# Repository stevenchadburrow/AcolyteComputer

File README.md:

# AcolyteComputer
Acolyte 6502 "Homebrew" Computer

Runs a W65C02 Microprocessor at 3.14 MHz.
Has 64K SRAM and 32K FlashROM.

VGA resolution of 320x240 4-Colors.
PS/2 Keyboard support built in.
One-voice square wave audio.
SPI EEPROM is built into the board.
Socket for a MicroSD Card Adapter.
Optional VIA Expansion.
It is powered with 5V USB.

The goal is that this board would cost less than $100 to assemble.
There are also no CPLD or FPGA chips used, everything besides the 6502/RAM/ROM are 74HC' logic chips.

All files included here are hereby released into the Public Domain.  Anyone is free to copy, modify, publish, use, compile, sell, or distribute these files for any purpose, commercial or non-commercial, and by any means.  These files are provided "as is", without warranty of any kind.  In no event shall the author be liable for any claim, damages, or other liability.

<br>
<br>
<br>
<br>

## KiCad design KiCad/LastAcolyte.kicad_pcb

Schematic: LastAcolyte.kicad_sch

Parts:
C1: C_Polarized_US; Dual Capacitor (Medium)
C2: C-Polarized-US; Dual Electrolytic Capacitor
C3, C4, C5, C6, C7, C8, C9, C10, C11, C12, C13, C14, C15, C16, C17, C18, C19, C20, C21, C22: C; C_Disc_D5.0mm_W2.5mm_P5.00mm
D1: LED; CustomLED
D2, D3: D; WideDiode
J1: USB_B; DualPowerSupply
J2: Mini-DIN-6; PS2_Din6
J3: AudioJack3; BIGJack_3.5mm_Ledino_KB3SPRS_Horizontal
J4: DB15_Female_HighDensity; DSUB-15-HD_Female_Horizontal_P2.29x2.54mm_VGA
J5: Conn-01x06; SDcardPinSocket-Wide
J6: Conn_01x02; PinHeader_1x02_P2.54mm_Vertical
J7: Conn_02x20_Odd_Even; PinSocket_2x20_P2.54mm_Vertical
JP1, JP2: SolderJumper_2_Open; SolderJumper_Testing-2_P1.3mm_Open_Pad1.0x1.5mm
Q1, Q2, Q3: PN2222A; TO-92_HandSolder
R1, R4, R5, R6, R7, R8, R9, R10, R11, R12, R13, R14, R16, R17, R18, R19, R20: R_US; R_Axial_DIN0207_L6.3mm_D2.5mm_P7.62mm_Horizontal
R2, R3: R-US; R_Axial_DIN0207_L6.3mm_D2.5mm_P7.62mm_Horizontal
SW1: SW_SPDT; SPDT-1MS1T1B4M7QES
SW2: SW_Push; SW_Tactile_SPST_Angled_PTS645Vx83-2LFS
TP1, TP2, TP3, TP4, TP5: TestPoint; ScrewHole-4-40
TP6, TP7: TestPoint; CustomTestPoint
U1: W65C02SxP; DIP-40_W15.24mm_Socket
U2: AS6C4008-55PCN; DIP-32_W15.24mm_Socket
U3: SST39SF040; DIP-32_W15.24mm_Socket
U4: 74HC161; DIP-16_W7.62mm_Socket
U5, U6, U7: 74HC590; DIP-16_W7.62mm_Socket
U8: 74HC245; DIP-20_W7.62mm_Socket
U9: 74HC273; DIP-20_W7.62mm_Socket
U10: 74HC377; DIP-20_W7.62mm_Socket
U11, U12: 74HC166; DIP-16_W7.62mm_Socket
U13: 74HC10; DIP-14_W7.62mm_Socket
U14: 74HC08; DIP-14_W7.62mm_Socket
U15: 74HC00; DIP-14_W7.62mm_Socket
U16: 74HC02; DIP-14_W7.62mm_Socket
U17: MCP130-xxxDxTO; TO-92_HandSolder
U18: 25LCxxx; DIP-8_W7.62mm_Socket
X1: CXO_DIP8/14; DualOscillator

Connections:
+5V: C1.1, C3.1, C4.1, C5.1, C6.1, C7.1, C8.1, C9.1, C10.1, C11.1, C12.1, C13.1, C14.1, C15.1, C16.1, C17.1, C18.1, C19.1, C20.1, C21.1, C22.1, J2.4, J5.2, J6.1, J7.1, J7.40, JP1.1 (A), JP2.2 (B), R1.2, R4.1, R5.1, R6.1, R7.2, R8.2, R16.2, R17.1, R18.1, R19.1, R20.2, SW1.2 (B), U1.8 (VDD), U2.1 (A18), U2.30 (A17), U2.32 (VCC), U3.1 (A18), U3.30 (A17), U3.31 (PGM), U3.32 (VCC), U4.1 (~MR), U4.3 (D0), U4.4 (D1), U4.5 (D2), U4.6 (D3), U4.7 (CEP), U4.9 (~PE), U4.10 (CET), U4.16 (VCC), U5.16 (VCC), U6.16 (VCC), U7.16 (VCC), U8.20 (VCC), U9.20 (VCC), U10.20 (VCC), U11.16 (VCC), U12.16 (VCC), U13.14 (VCC), U14.14 (VCC), U15.14 (VCC), U16.14 (VCC), U17.2 (VDD), U18.3 (~WP), U18.7 (~HOLD), U18.8 (VCC), X1.11 (Vcc), X1.14 (Vcc)
/D0: U1.33 (D0), U3.13 (D0), U8.18 (B0), U9.3 (D0), U10.3 (D0)
/D1: U1.32 (D1), U3.14 (D1), U8.17 (B1), U9.4 (D1), U10.4 (D1)
/D2: U1.31 (D2), U3.15 (D2), U8.16 (B2), U9.7 (D2), U10.7 (D2)
/D3: U1.30 (D3), U3.17 (D3), U8.15 (B3), U9.8 (D3), U10.8 (D3)
/D4: U1.29 (D4), U3.18 (D4), U8.14 (B4), U9.13 (D4), U10.13 (D4)
/D5: U1.28 (D5), U3.19 (D5), U8.13 (B5), U9.14 (D5), U10.14 (D5)
/D6: U1.27 (D6), U3.20 (D6), U8.12 (B6), U9.17 (D6), U10.17 (D6)
/D7: U1.26 (D7), U3.21 (D7), U8.11 (B7), U9.18 (D7), U10.18 (D7)
A0: J7.38, U1.9 (A0), U2.12 (A0), U3.12 (A0), U5.15 (Q0)
A1: J7.36, U1.10 (A1), U2.11 (A1), U3.11 (A1), U5.1 (Q1)
A2: J7.34, U1.11 (A2), U2.10 (A2), U3.10 (A2), U5.2 (Q2)
A3: J7.32, U1.12 (A3), U2.9 (A3), U3.9 (A3), U5.3 (Q3)
A4: J7.30, U1.13 (A4), U2.8 (A4), U3.8 (A4), U5.4 (Q4)
A5: J7.28, U1.14 (A5), U2.7 (A5), U3.7 (A5), U5.5 (Q5)
A6: J7.26, U1.15 (A6), U2.6 (A6), U3.6 (A6), U5.6 (Q6)
A7: J7.24, U1.16 (A7), U2.5 (A7), U3.5 (A7), U6.1 (Q1)
A8: J7.18, U1.17 (A8), U2.27 (A8), U3.27 (A8), U6.2 (Q2)
A9: J7.16, U1.18 (A9), U2.26 (A9), U3.26 (A9), U6.3 (Q3)
A10: J7.14, U1.19 (A10), U2.23 (A10), U3.23 (A10), U6.4 (Q4)
A11: J7.12, U1.20 (A11), U2.25 (A11), U3.25 (A11), U6.5 (Q5)
A12: U1.22 (A12), U2.4 (A12), U3.4 (A12), U6.6 (Q6), U14.2
A13: U1.23 (A13), U2.28 (A13), U3.28 (A13), U6.7 (Q7), U14.1
A14: U1.24 (A14), U2.3 (A14), U3.29 (A14), U7.15 (Q0), U14.13, U16.2
A15: U1.25 (A15), U2.31 (A15), U3.3 (A15), U7.1 (Q1), U13.10, U14.12, U15.1
AUDIO-NEG: C2.2, R2.2
AUDIO-OUT: C2.1, J7.21, U9.19 (Q7)
AUDIO-TIP: J3.T, R2.1, R3.1
BE: U1.36 (BE), U1.39 (ϕ2)
BLUE: J4.3, R11.2, R14.2
C0: J7.3, U2.13 (DQ0), U8.2 (A0), U12.2 (A), U12.3 (B)
C1: J7.5, U2.14 (DQ1), U8.3 (A1), U11.2 (A), U11.3 (B)
C2: J7.7, U2.15 (DQ2), U8.4 (A2), U12.4 (C), U12.5 (D)
C3: J7.9, U2.17 (DQ3), U8.5 (A3), U11.4 (C), U11.5 (D)
C4: J7.11, U2.18 (DQ4), U8.6 (A4), U12.10 (E), U12.11 (F)
C5: J7.13, U2.19 (DQ5), U8.7 (A5), U11.10 (E), U11.11 (F)
C6: J7.15, U2.20 (DQ6), U8.8 (A6), U12.12 (G), U12.14 (H)
C7: J7.17, U2.21 (DQ7), U8.9 (A7), U11.12 (G), U11.14 (H)
CLK: J7.29, U4.2 (CP), U5.13 (CPR), U6.13 (CPR), U7.13 (CPR), U10.11 (CP), U11.7 (Clk), U12.7 (Clk), X1.8 (OUT)
ENABLE: JP1.2 (B), X1.1 (EN), X1.4 (EN)
GND: C1.2, C3.2, C4.2, C5.2, C6.2, C7.2, C8.2, C9.2, C10.2, C11.2, C12.2, C13.2, C14.2, C15.2, C16.2, C17.2, C18.2, C19.2, C20.2, C21.2, C22.2, D1.1 (K), J1.4 (GND), J1.5 (Shield), J1.7 (Barrel_GND), J2.3, J3.S, J4.5, J4.6, J4.7, J4.8, J4.10, J5.1, J6.2, J7.2, J7.19, J7.22, J7.39, Q1.1 (E), Q2.1 (E), R3.2, SW1.4 (Shield), SW2.2, TP1.1, TP2.1, TP3.1, TP4.1, TP5.1, TP6.1, TP7.1, U1.21 (VSS), U2.16 (VSS), U3.16 (GND), U4.8 (GND), U5.8 (GND), U5.12 (~CE), U6.8 (GND), U6.12 (~CE), U7.8 (GND), U8.10 (GND), U9.10 (GND), U10.10 (GND), U11.1 (Ds), U11.6 (CE), U11.8 (GND), U12.1 (Ds), U12.6 (CE), U12.8 (GND), U13.7 (GND), U14.7 (GND), U15.7 (GND), U16.7 (GND), U17.3 (VSS), U18.4 (GND), X1.7 (GND)
GREEN: J4.2, R10.2, R13.2
H-RESET: U5.10 (~MRC), U10.2 (Q0)
H-SYNC: J4.13, U10.12 (Q4)
HALF: J7.27, U4.14 (Q0), U13.1
HIGH: U14.11, U15.4, U16.9
IO-ENABLE: U9.15 (Q5), U16.3
IO-INT: D3.1 (K), J7.8, R20.1
KEY-CLK: J2.5, R4.2, U14.4
KEY-DATA: D2.1 (K), J2.1, R5.2
LED: D1.2 (A), R1.1
MEM-BANK: U3.2 (A16), U9.12 (Q4), U15.2
MID: U13.11, U14.3
NMI-ENABLE: U9.16 (Q6), U14.5
PHI2: J7.23, U1.37 (ϕ0), U4.12 (Q2), U5.11 (CPC), U5.14 (~OE), U6.14 (~OE), U7.14 (~OE), U15.9
PIXA: R9.1, R10.1, R11.1, U11.13 (Qh)
PIXB: R12.1, R13.1, R14.1, U12.13 (Qh)
POWER-IN: J1.1 (VBUS), J1.6 (Barrel_VCC), JP2.1 (A), SW1.1 (A)
QUARTER: J7.25, U4.13 (Q1), U13.2, U13.3
RAMADDR: U13.5, U14.8, U16.11
RAMEXP: U2.2 (A16), U15.3
RDY: J7.31, R7.1, U1.2 (RDY)
RED: J4.1, R9.2, R12.2
SIXTEENTH: U4.11 (Q3), U15.13
SPI-CLK: J5.5, U9.2 (Q0), U18.6 (SCK)
SPI-EEPROM: U9.6 (Q2), U18.1 (~CS)
SPI-MISO: J7.4, Q1.2 (B), Q3.1 (E), R8.1, U18.2 (MISO)
SPI-MOSI: J5.4, U9.5 (Q1), U18.5 (MOSI)
SPI-SDCARD: J5.6, Q2.2 (B), U9.9 (Q3)
SPI-SDCARD-MISO: J5.3, Q3.3 (C)
SYNC: J7.37, U1.7 (SYNC)
V-BLANK: U10.19 (Q7)
V-RESET: U6.10 (~MRC), U7.10 (~MRC), U10.6 (Q2)
V-SYNC: J4.14, U10.15 (Q5)
VISIBLE: U10.16 (Q6), U11.9 (Clr), U12.9 (Clr)
~A14: U13.9, U16.1
~CE: U8.19 (CE), U15.8
~H-RESET: U6.11 (CPC), U7.11 (CPC), U10.5 (Q1)
~IO: J7.10, U13.8, U14.9
~IRQ: D2.2 (A), D3.2 (A), R16.1, U1.4 (~IRQ)
~LATCH: U10.1 (~E), U11.15 (PE), U12.15 (PE), U13.12
~NMI: U1.6 (~NMI), U14.6
~OE: J7.33, U2.24 (OE#), U3.24 (OE), U13.4, U15.5, U16.4
~OUTPUT: U9.11 (Cp), U15.6
~PHI2: U1.3 (ϕ1), U13.13, U16.5, U16.8, U16.12
~RAM: U2.22 (CE#), U16.13
~RCO: U6.9 (~RCO), U7.12 (~CE)
~RES: J7.6, R18.2, SW2.1, U1.40 (~RES), U9.1 (~Mr), U17.1 (~RST)
~ROM: U3.22 (CE), U14.10, U15.10, U16.10
~RW: J7.35, R6.2, U1.34 (R/~W), U8.1 (A->B), U16.6
~SO: U1.38 (~SO), U15.11
~SPI-MISO: Q1.3 (C), R17.2, U15.12
~SPI-SDCARD: Q2.3 (C), Q3.2 (B), R19.2
~V-RESET: U10.9 (Q3)
~WE: U2.29 (WE#), U13.6

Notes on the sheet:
W65C02 running at 3.14 MHz 2KB System RAM 30KB Video RAM 12KB Banked RAM 4KB I/O (or RAM) 16KB Banked ROM
Video signals from ROM.
0.1uF Bypass Capacitors near VCC of each IC
Acolyte Computer Steven Chad Burrow 2023, Public Domain
~{CS2}
EXPANSION
Reading from RAM
(910)
Can also use AS6C1008, (and the 62256)
Optional Resistor
$8380
Can also use SST39SF010, (and the 27C512)
RS0
1-Voice Audio Out
Micro SD Card Adapter
RS3
$0000
Can also use 74HC163
Upper/Lower Addresses
Video
Visible Area
The xxxD pinout is important! Can also use DS1813. (Resistor could replace MCP130, but has potential for issues.)
(510)
Start Bit=0
Horizontal Back Porch
Can use 1N4148
Writing to RAM
Horizontal Front Porch
Horizontal Sync
Write Byte
Supports both DIP-8 and DIP-14 oscillators.
VGA Output
(100k)
$8000
Writing to ROM makes output.
Pull-up resistors
R/~{W}
~{RES}
Read Command
Writing to ROM (causes Output)

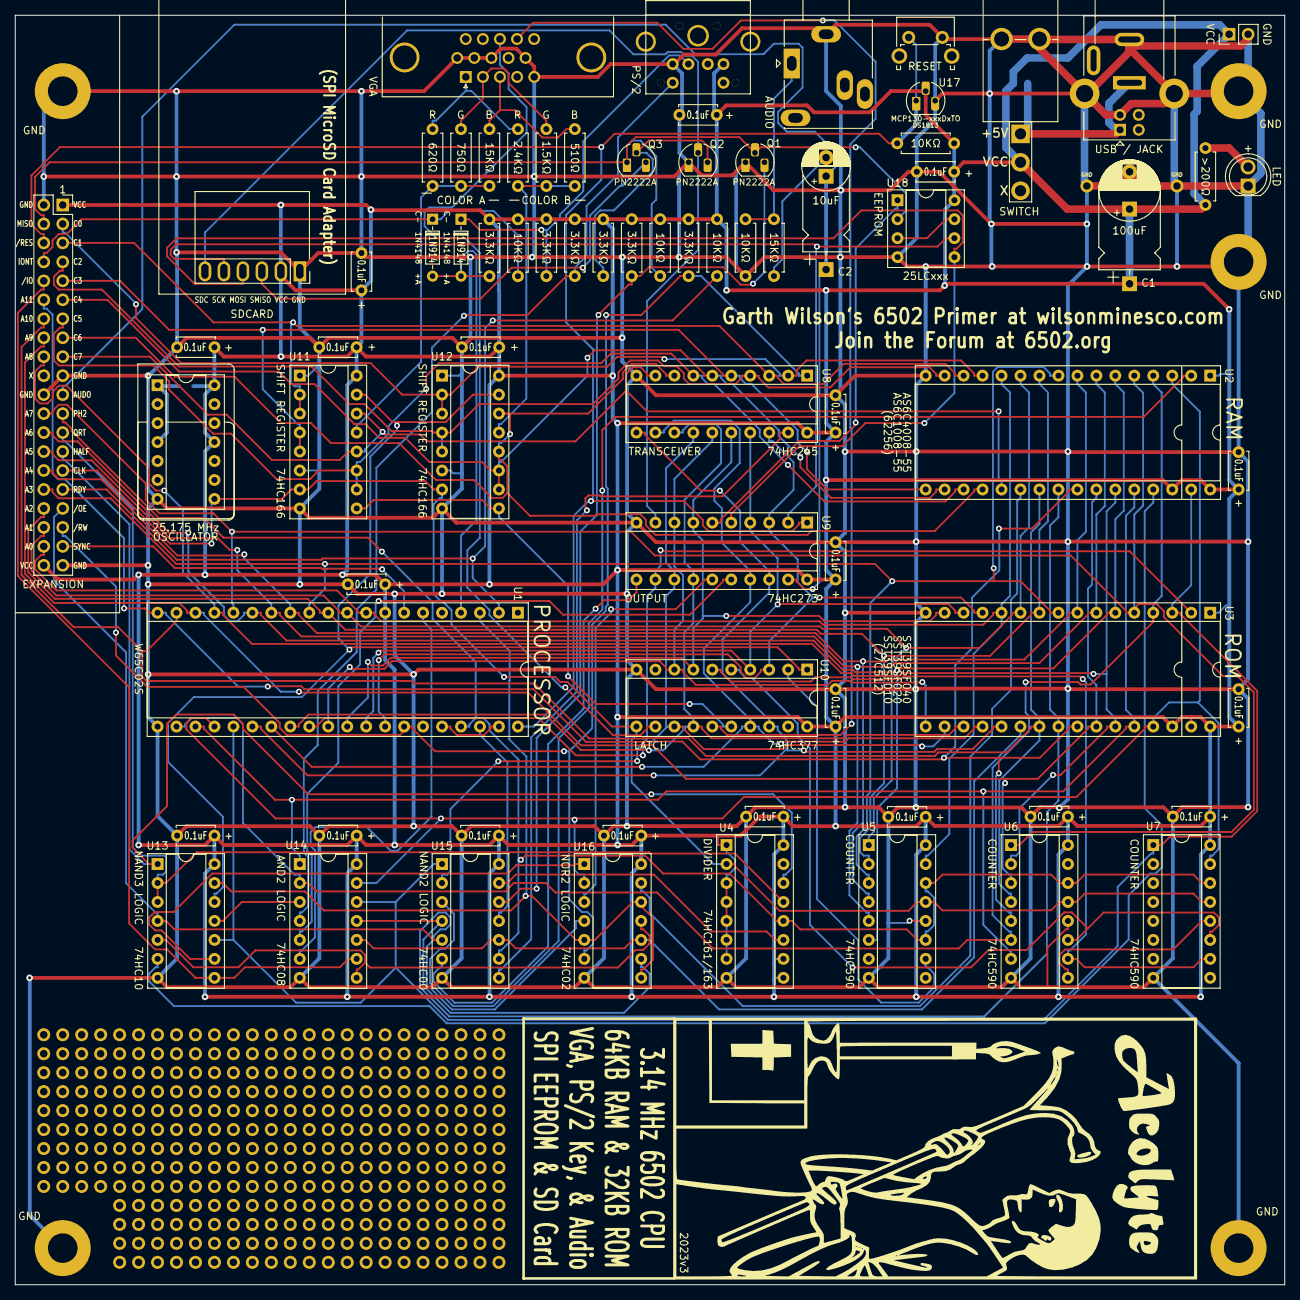
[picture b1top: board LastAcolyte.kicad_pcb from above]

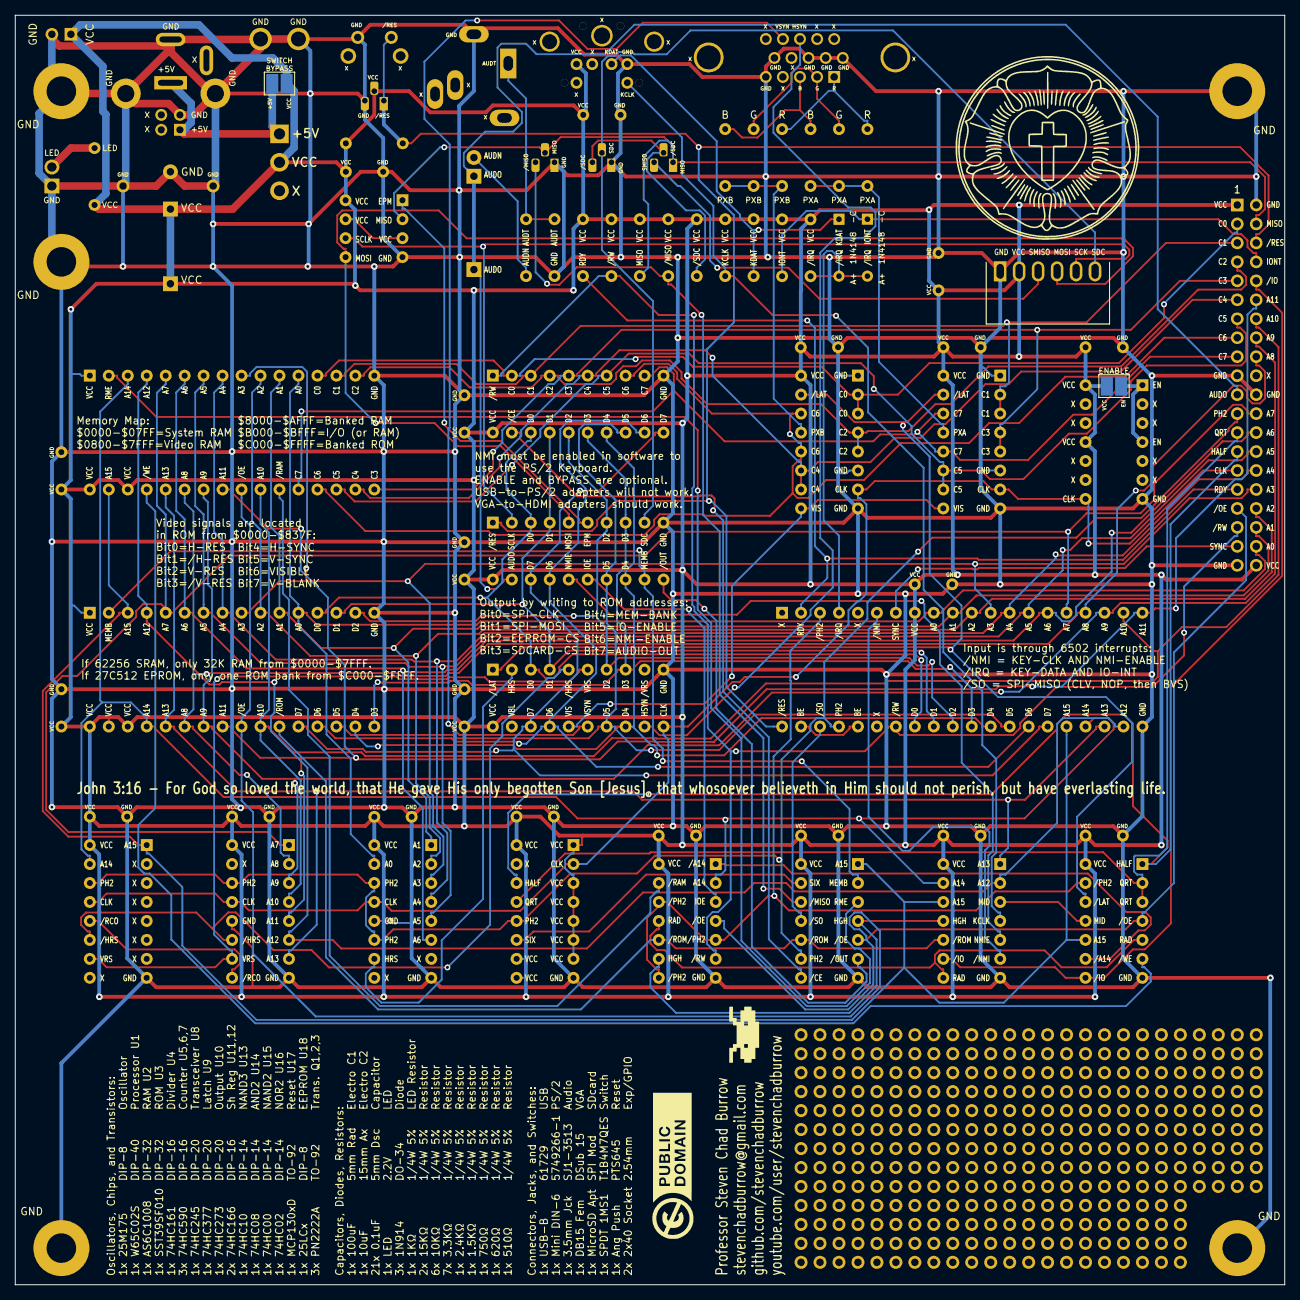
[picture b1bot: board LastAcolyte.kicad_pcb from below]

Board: 2 copper layers, 170.0 x 170.0 mm, 88 parts (5 on the bottom side), 93 nets.

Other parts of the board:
G99: LOGO; AcolyteLogoSmall
G995: LOGO; LutheranRosePD
G997: LOGO; Mystery
G998: LOGO; PublicDomain

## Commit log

2023-02-01 Rename AcolyteCode-Bank1.asm to Code/AcolyteCode-Bank1.asm
2023-02-01 Rename AcolyteCode-Bank2.asm to Code/AcolyteCode-Bank2.asm
2023-02-01 Rename AcolyteCode-Bank1.asm to Binaries/AcolyteCode-Bank1.asm
2023-02-01 Rename AcolyteCode-Bank1.asm to Schematics/AcolyteCode-Bank1.asm
2023-02-01 Rename SDcardCode1.asm to KiCad/SDcardCode1.asm
2023-02-01 Rename SDcardCode1.asm to Pictures/SDcardCode1.asm
2025-11-08 Rename OldAcolyte-Front.jpg to OldAcolyteV1-Front.jpg
2025-11-08 Rename OldAcolyte-Back.jpg to OldAcolyteV1-Back.jpg
